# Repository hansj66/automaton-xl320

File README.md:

# automaton-xl320
Dynamixel controller for AX-12A/W, XL-320 with IMU and BT

## Note:
* This repo contains the Eagle schematics and PCB laout for a functional dynamixel controller. The board is still in early development and the design is subject to change. Clone & build at your own risk :)
* Firmware example for a [XL-320 based balancing bot](https://github.com/hansj66/automaton-xl320/tree/main/hardware/fusion/balance-bot) can be found [here](https://github.com/hansj66/automaton-xl320/blob/main/firmware/esp/balance-bot/src/main.cpp).
* The mechanical design for an AX-12A hexapod is complete, but the firmware is still in early development
* Alexa integration is still in the "ripoff a sample" stage
* The board can be assembled by hand relatively easy, using a stencil, low temperature T3/T4 paste and a hot plate.
* There is no battery monitoring circuitry on the board. Undervoltage detection for a given battery type and automatic shutdown can be achieved by using the MIN_VOLTAGE_LIMIT and SHUTDOWN registers in the dynamixel control table.
* The board is BT and Thread capable, but integration between the nRF and the ESP is currently limited to I2C + one GPIO line.

## Stuff that is subject to change in future revision
* nRF/ESP integration
* Expansion header

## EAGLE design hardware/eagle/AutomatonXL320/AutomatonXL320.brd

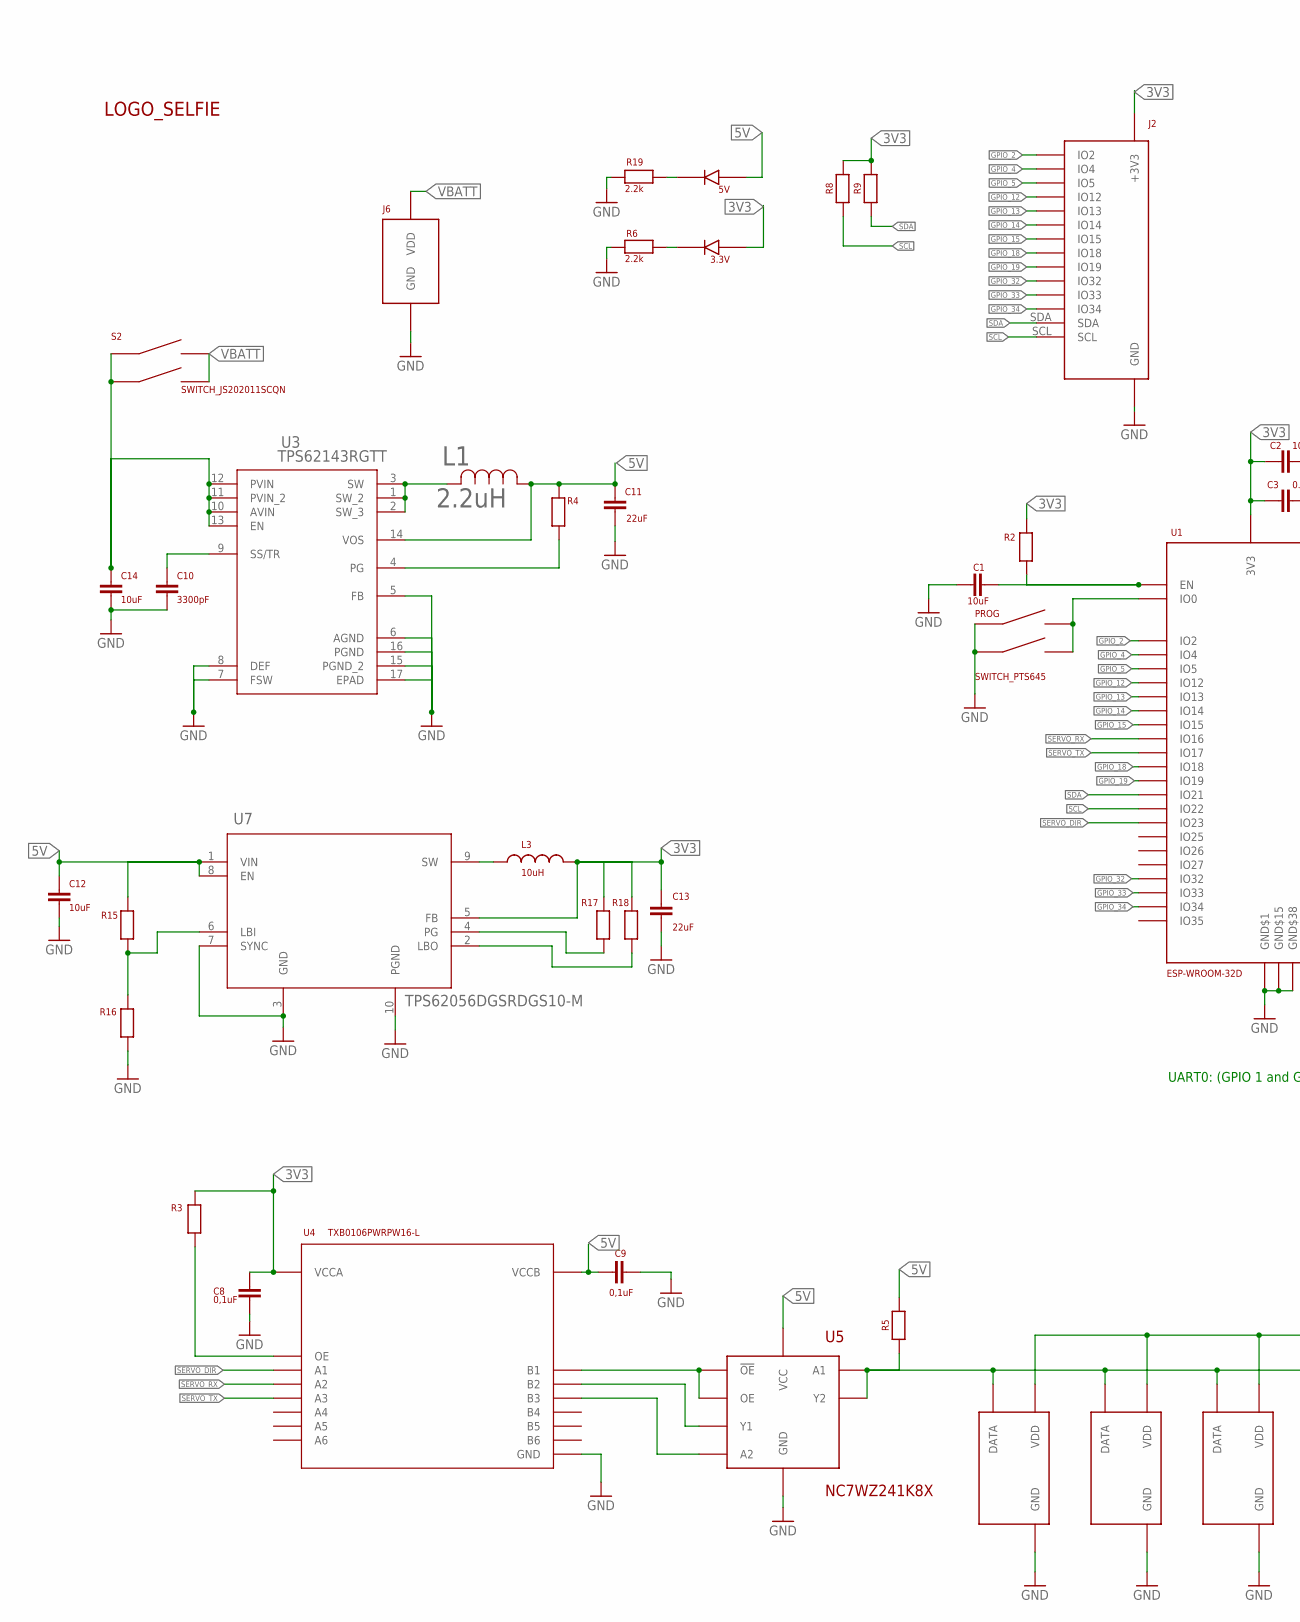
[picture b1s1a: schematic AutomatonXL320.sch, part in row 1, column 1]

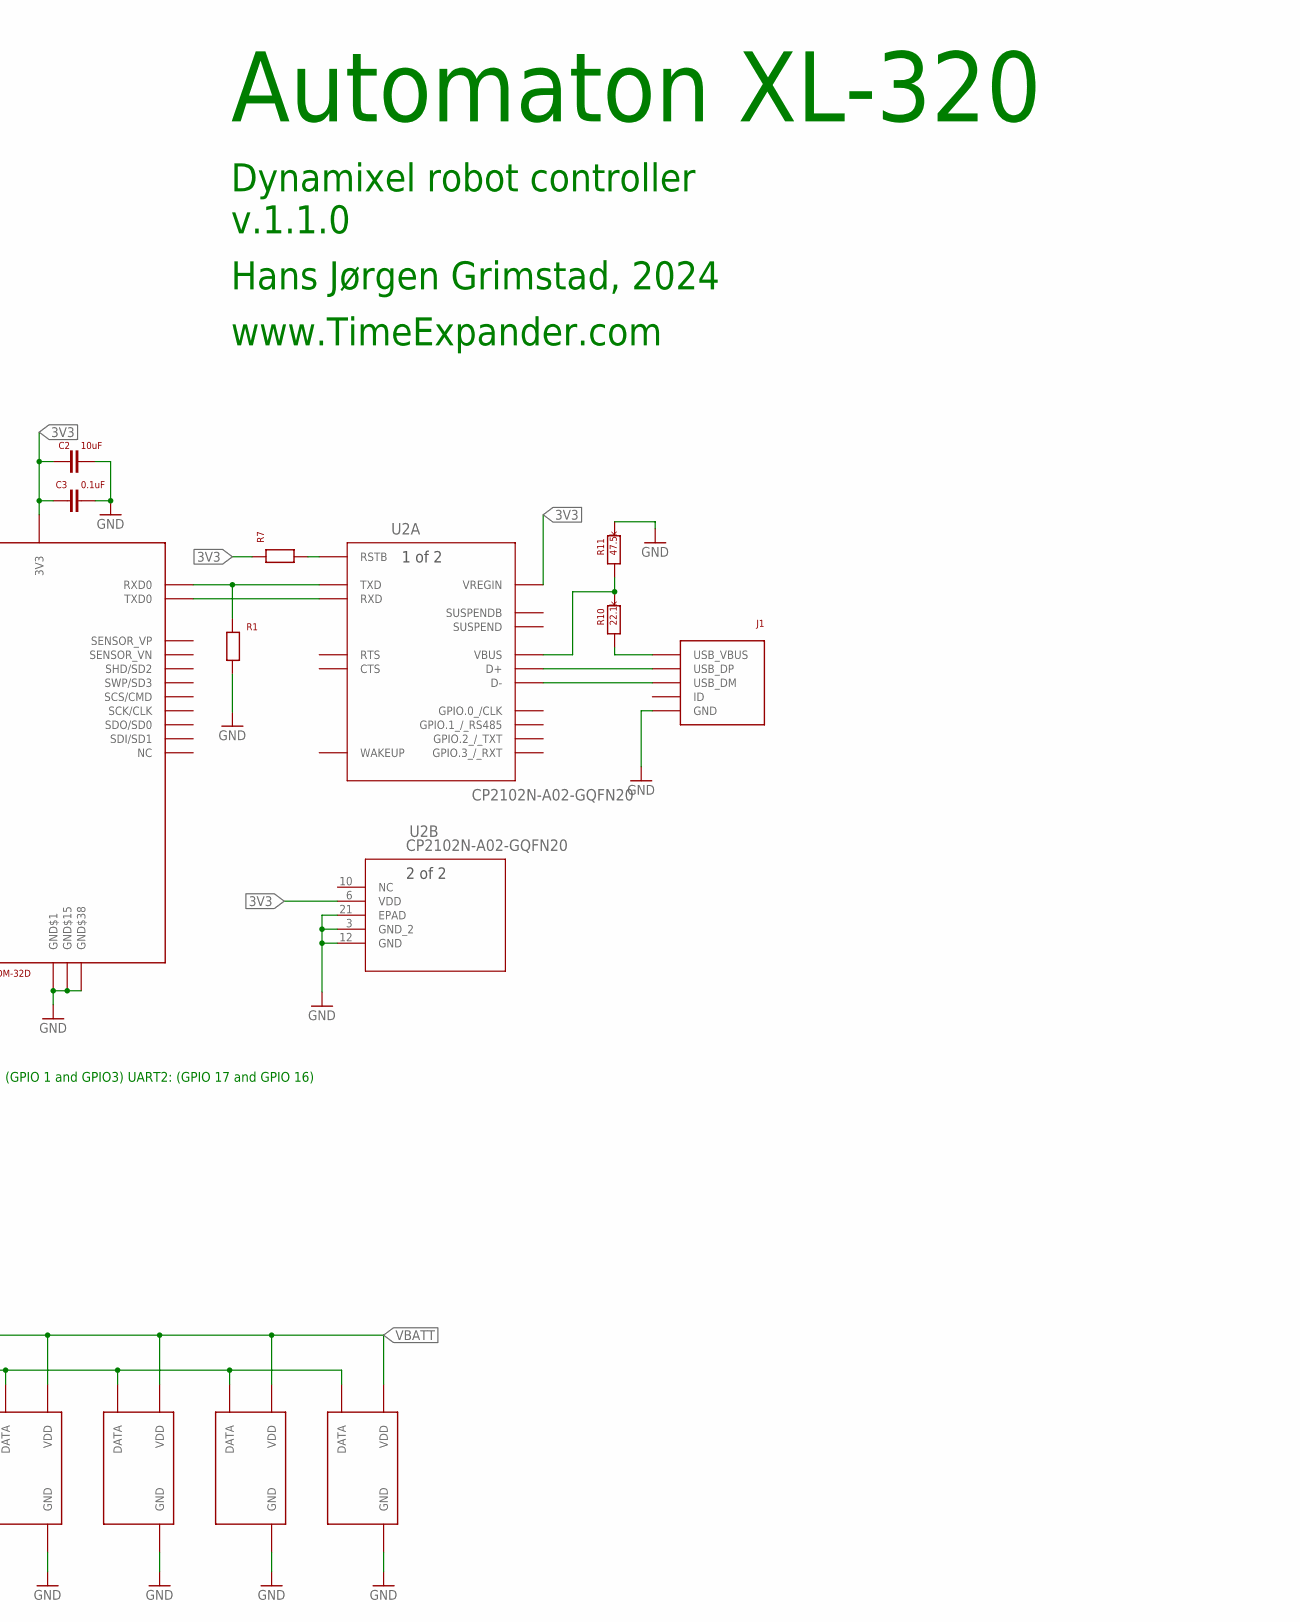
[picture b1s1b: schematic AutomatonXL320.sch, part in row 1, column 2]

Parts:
3.3V, 5V: LED_APTR3216PBC/A
C1, C2: 10uF; CAP_0402
C3: 0.1uF; CAP_0402
C8, C9: 0,1uF; CAP_0402
C10: 3300pF; CAP_0402
C11, C13: 22uF; CAP_1206
C12, C14: 10uF; CAP_1206
J1: USB_RCPT_10118192-0001LF
J2: ESP_ROBOT_BOARD_GPIO_16
J6: BATTERY; BATTERY_SOLDER_TERMINAL
L1: 2.2uH; IND_IHLP-1616AB-M
L3: 10uH; IND_4028
PROG: SWITCH_PTS645; SWITCH_PTS645_EE_NBIOT_01
R1, R2, R3, R4, R5, R7, R8, R9, R15, R16, R17, R18: RESISTOR0402; RES_0402
R6, R19: 2.2k; RES_0402
R10: 22.1k; RES_0402
R11: 47.5k; RES_0402
S2: SWITCH_JS202011SCQN
U1: ESP-WROOM-32D; ESP_WROOM_32D
U2: CP2102N-A02-GQFN20; QFN20_CP2102N_SIL
U3: TPS62143RGTT; RGT16_1P7X1P7
U4: TXB0106PWRPW16-L; PW16-L
U5: NC7WZ241K8X
U7: TPS62056DGSRDGS10-M; DGS10-M
U$1, U$4, U$5, U$6, U$8, U$9: DYNAMIXEL_MOLEX_MINISPOX_3P_HEADERXL-320; DYNAMIXEL_MICROLATCH_3P_HEADER
U$2: LOGO_SELFIESELFIE_2; TIMEEXPANDER_LOGO_1

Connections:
3V3: 3.3V.A, C2.P$1 (1), C3.P$1 (1), C8.P$2 (2), C13.P$1 (1), J2.+3V3, L3.2, R2.P$2, R3.P$2, R7.P$1, R8.P$2, R9.P$2, R17.P$2, R18.P$2, U1.2 (3V3), U2.6 (VDD), U2.7 (VREGIN), U4.2 (VCCA), U7.5 (FB)
5V: 5V.A, C9.P$1 (1), C11.P$1 (1), C12.P$1 (1), L1.1, R4.P$2, R5.P$2, R15.P$2, U3.14 (VOS), U4.15 (VCCB), U5.VCC, U7.1 (VIN), U7.8 (EN)
GND: C1.P$1 (1), C2.P$2 (2), C3.P$2 (2), C8.P$1 (1), C9.P$2 (2), C10.P$2 (2), C11.P$2 (2), C12.P$2 (2), C13.P$2 (2), C14.P$2 (2), J1.GND, J2.GND, J6.- (GND), PROG.A1, PROG.A2, R1.P$2, R6.P$1, R11.P$2, R16.P$1, R19.P$1, U1.1 (GND$1), U1.15 (GND$15), U1.38 (GND$38), U1.GND$39 (GND$38), U1.GND$40 (GND$38), U1.GND$41 (GND$38), U1.GND$42 (GND$38), U1.GND$43 (GND$38), U1.GND$44 (GND$38), U1.GND$45 (GND$38), U1.GND$46 (GND$38), U1.GND$47 (GND$38), U2.3 (GND_2), U2.12 (GND), U2.21 (EPAD), U3.5 (FB), U3.6 (AGND), U3.7 (FSW), U3.8 (DEF), U3.15 (PGND_2), U3.16 (PGND), U3.17 (EPAD), U4.9 (GND), U5.GND, U7.3 (GND), U7.7 (SYNC), U7.10 (PGND), U$1.GND, U$4.GND, U$5.GND, U$6.GND, U$8.GND, U$9.GND
GPIO_2: J2.IO2, U1.24 (IO2)
GPIO_4: J2.IO4, U1.26 (IO4)
GPIO_5: J2.IO5, U1.29 (IO5)
GPIO_12: J2.IO12, U1.14 (IO12)
GPIO_13: J2.IO13, U1.16 (IO13)
GPIO_14: J2.IO14, U1.13 (IO14)
GPIO_15: J2.IO15, U1.23 (IO15)
GPIO_18: J2.IO18, U1.30 (IO18)
GPIO_19: J2.IO19, U1.31 (IO19)
GPIO_32: J2.IO32, U1.8 (IO32)
GPIO_33: J2.IO33, U1.9 (IO33)
GPIO_34: J2.IO34, U1.6 (IO34)
unnamed: C1.P$2 (2), R2.P$1, U1.3 (EN)
unnamed: 3.3V.C, R6.P$2
unnamed: C10.P$1 (1), U3.9 (SS/TR)
unnamed: R1.P$1, U1.34 (RXD0), U2.18 (TXD)
unnamed: U1.35 (TXD0), U2.17 (RXD)
unnamed: PROG.B1, PROG.B2, U1.25 (IO0)
unnamed: L1.2, U3.1 (SW_2), U3.2 (SW_3), U3.3 (SW)
unnamed: U4.16 (B1), U5.!OE, U5.OE
unnamed: R4.P$1, U3.4 (PG)
unnamed: U4.14 (B2), U5.Y1
unnamed: U4.13 (B3), U5.A2
unnamed: R7.P$2, U2.9 (RSTB)
unnamed: C14.P$1 (1), S2.2 (A2), S2.5 (A1), U3.10 (AVIN), U3.11 (PVIN_2), U3.12 (PVIN), U3.13 (EN)
unnamed: R3.P$1, U4.8 (OE)
unnamed: J1.VCC (USB_VBUS), R10.P$1
unnamed: J1.D+ (USB_DP), U2.4 (D+)
unnamed: J1.D- (USB_DM), U2.5 (D-)
unnamed: R10.P$2, R11.P$1, U2.8 (VBUS)
unnamed: R5.P$1, U5.A1, U5.Y2, U$1.DATA, U$4.DATA, U$5.DATA, U$6.DATA, U$8.DATA, U$9.DATA
unnamed: 5V.C, R19.P$2
unnamed: R15.P$1, R16.P$2, U7.6 (LBI)
unnamed: L3.1, U7.9 (SW)
unnamed: R17.P$1, U7.4 (PG)
unnamed: R18.P$1, U7.2 (LBO)
SCL: J2.SCL, R8.P$1, U1.36 (IO22)
SDA: J2.SDA, R9.P$1, U1.33 (IO21)
SERVO_DIR: U1.37 (IO23), U4.1 (A1)
SERVO_RX: U1.27 (IO16), U4.3 (A2)
SERVO_TX: U1.28 (IO17), U4.4 (A3)
VBATT: J6.+ (VDD), S2.3 (B2), S2.6 (B1), U$1.VDD, U$4.VDD, U$5.VDD, U$6.VDD, U$8.VDD, U$9.VDD

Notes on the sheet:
Automaton XL-320
Dynamixel robot controller
v.1.1.0
Hans Jørgen Grimstad, 2024
www.TimeExpander.com
UART0: (GPIO 1 and GPIO3) UART2: (GPIO 17 and GPIO 16)

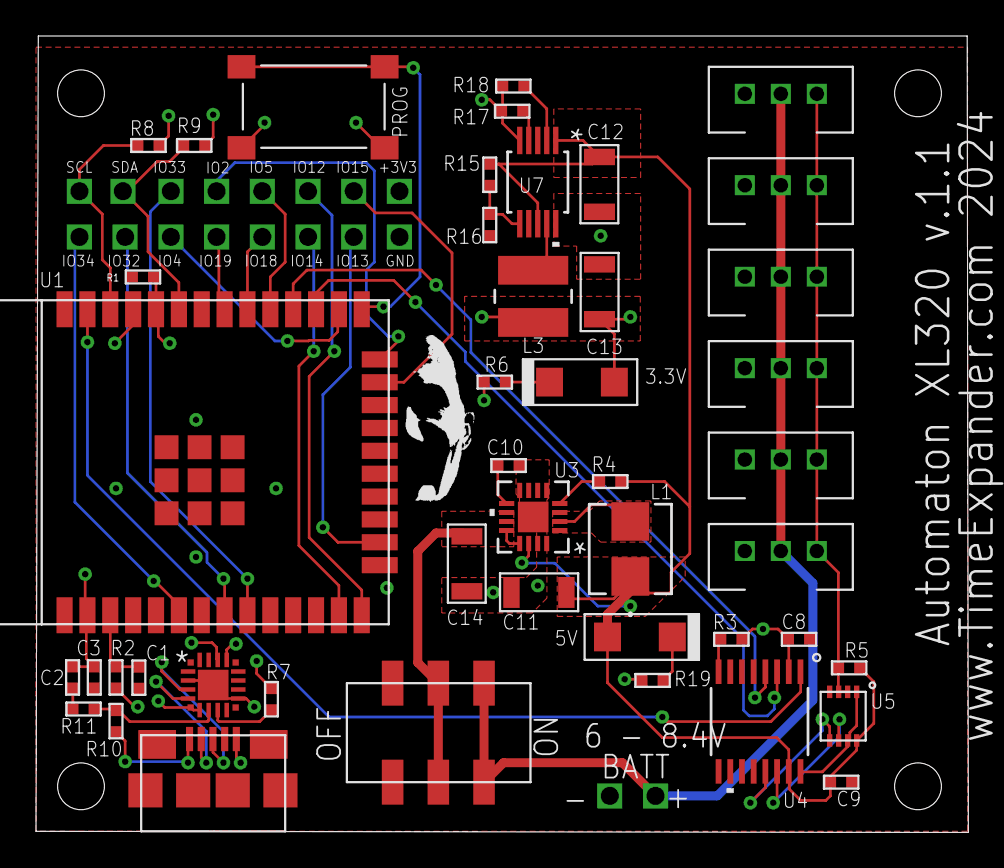
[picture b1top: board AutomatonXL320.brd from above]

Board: 4 copper layers, 51.8 x 44.2 mm, 48 parts (0 on the bottom side), 45 nets.

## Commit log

2021-11-14 Added display, nvs, calibration
2021-11-28 Added web PID control
    * Changed PID algorithm
    * Displaying QR code with URL
2021-12-04 Added NVS save + load of PID params
    * Updated config page with boogie + greet buttons
    * Not forcing recalibration at normal rest position
    * Commented out kalman stuff
    * Added sensible default PID values
    * Added greet + boogie handlers to mux
    * Slowed down Rise() function
2021-12-13 Slowed down the raise speed
2021-12-13 Updated README with suggested initial PID parameters
2021-12-13 Updated STL and STEP files
    * Balance bot
2021-12-13 Removed old picture
2021-12-13 Removed dead autotuning code
    * Would have taken too long to converge anyway
2024-02-20 Added new (smaller) board
    * Only XL-320
2024-04-30 CP2102N VBUS is now connected via resistor ladder
    * CP2102N was overheating at times because it was
    connected directly to USB VBUS

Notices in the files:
parts and their libraries:
COPYRIGHT: Copyright (C) 2023 Ultra Librarian. All rights reserved.
